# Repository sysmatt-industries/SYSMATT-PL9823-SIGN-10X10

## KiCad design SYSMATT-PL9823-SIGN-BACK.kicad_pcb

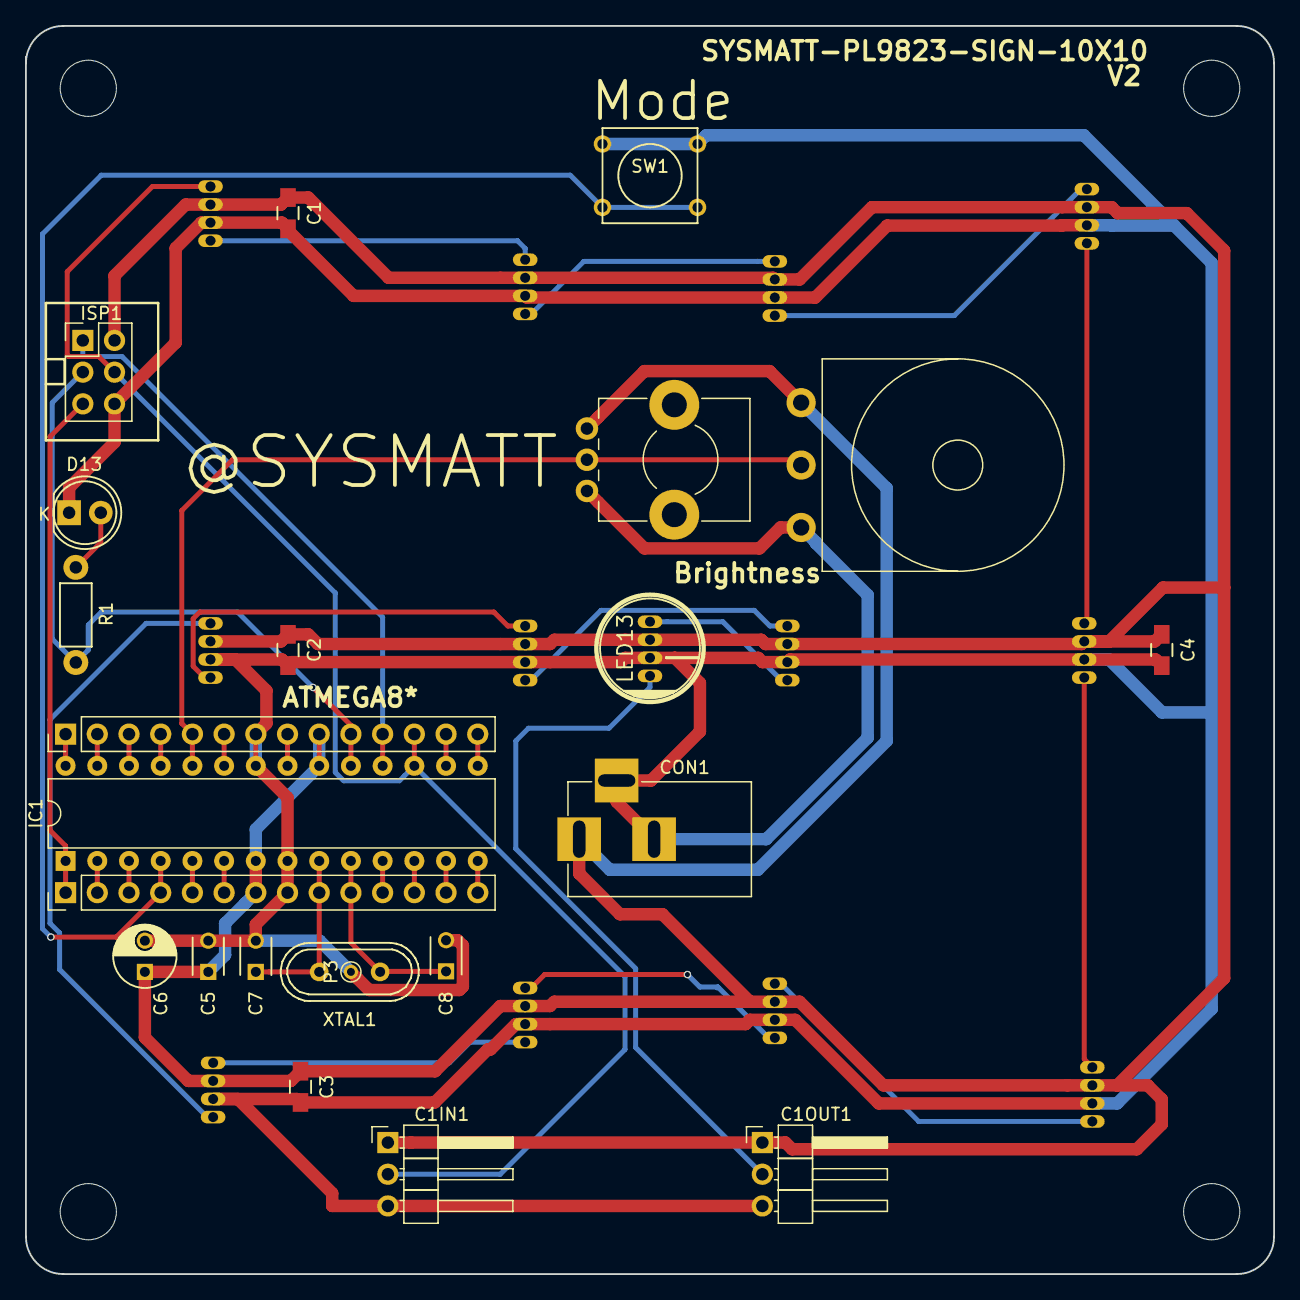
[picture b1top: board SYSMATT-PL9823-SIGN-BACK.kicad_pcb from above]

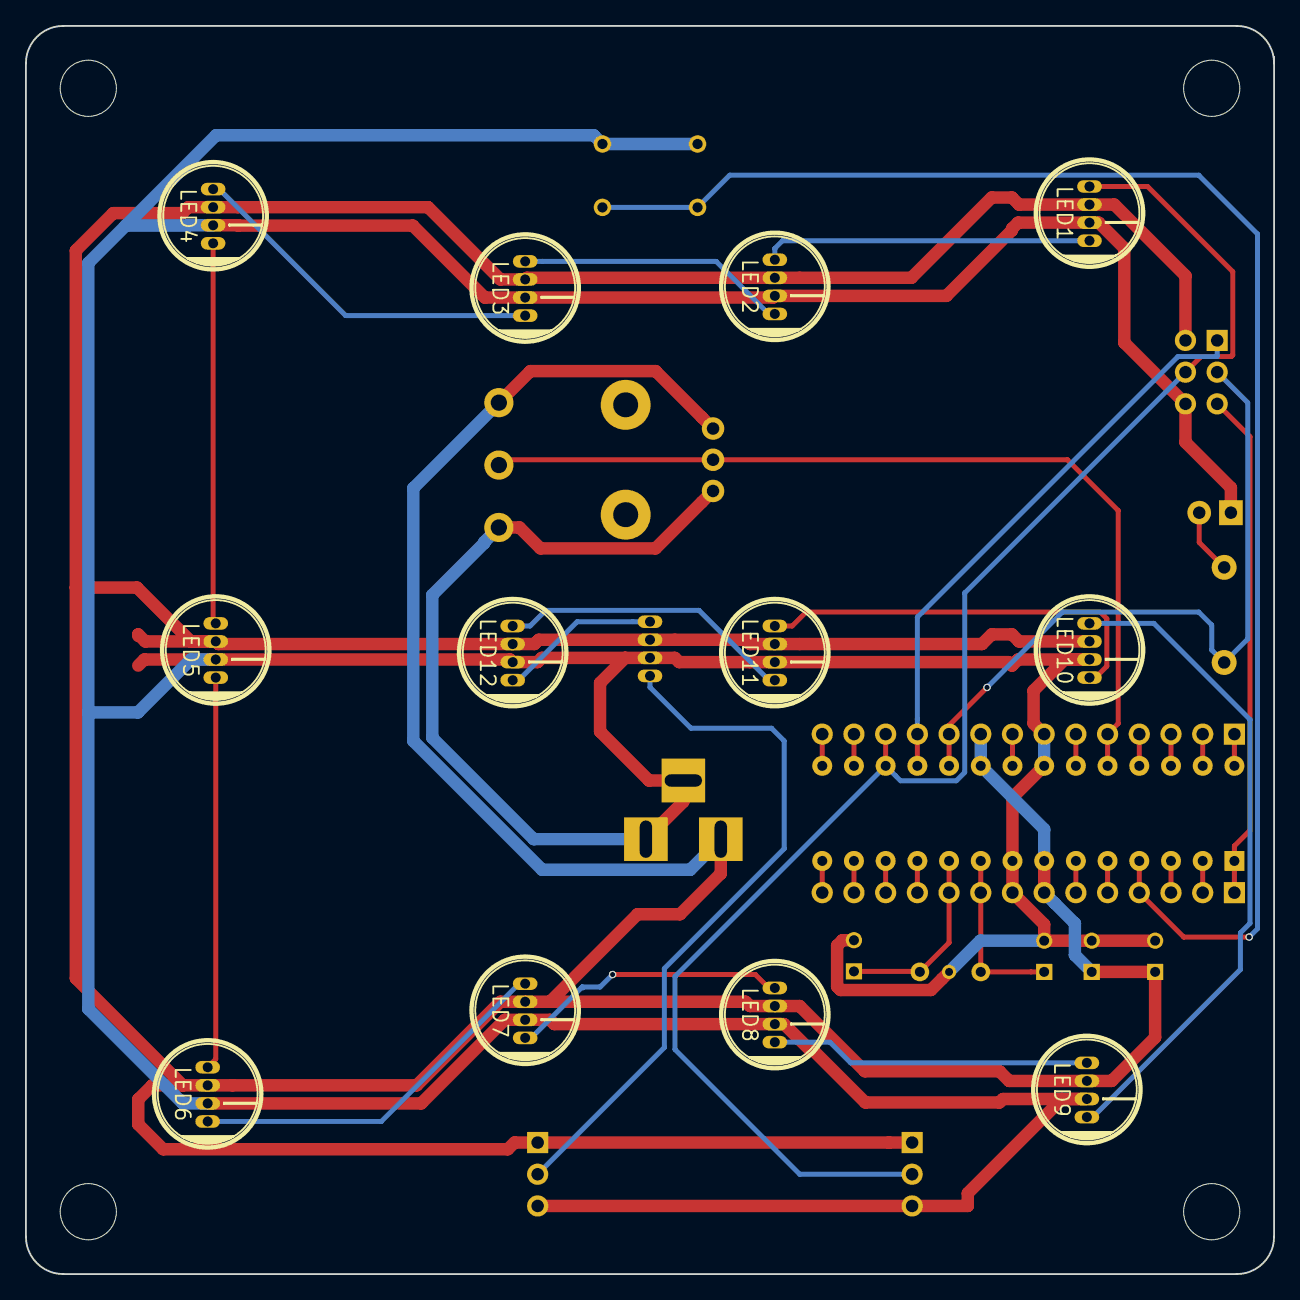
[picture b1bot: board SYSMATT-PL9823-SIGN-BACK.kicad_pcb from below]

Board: 2 copper layers, 100.0 x 100.0 mm, 35 parts (12 on the bottom side), 40 nets.

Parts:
C1, C2, C3, C4: CP1_Small; C_0805_HandSoldering
C1IN1, C1OUT1: CONN_01X03; Pin_Header_Angled_1x03_Pitch2.54mm
C5, C7, C8: C; C_Disc_D3_P2.5
C6: CP1; C_Radial_D5_L6_P2.5
CON1: BARREL_JACK
D13: LED; LED-5MM
IC1: ATMEGA8-P; DIP-28_W7.62mm
ISP1: CONN_02X03; Pin_Header_Straight_2x03_Pitch2.54mm
LED1, LED2, LED3, LED4, LED5, LED6, LED7, LED8, LED9, LED10, LED11, LED12, LED13: PL9823; PL9823-SYSMATT-V4
P1, P2: CONN_01X14; Pin_Header_Straight_1x14_Pitch2.54mm
P3: CONN_01X01; PINTST
R1: R; Resistor_Horizontal_RM7mm
RV1: POT; Potentiometer_Bourns_PTV09A-1_Horizontal
RV2: POT; Potentiometer_Omeg_PC16PU_Horizontal
SW1: SW_PUSH; SW_PUSH_SMALL
XTAL1: Crystal; Crystal_HC49-U_Vertical

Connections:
/DIN: C1IN1.2, IC1.17, ISP1.4, LED1.1, P2.12
/DOUT: C1OUT1.2, LED13.4
/SYSMATT-ATMEGA-ASP-BO/ATMEGA_ANALOG_POT: IC1.24, P2.5, RV1.2, RV2.2
/SYSMATT-ATMEGA-ASP-BO/ATMEGA_BUTTON_IN: IC1.4, P1.4, SW1.2
/SYSMATT-ATMEGA-ASP-BO/P1: IC1.1, ISP1.5, P1.1
/SYSMATT-ATMEGA-ASP-BO/P2: IC1.2, P1.2
/SYSMATT-ATMEGA-ASP-BO/P3: IC1.3, P1.3
/SYSMATT-ATMEGA-ASP-BO/P5: IC1.5, P1.5
/SYSMATT-ATMEGA-ASP-BO/P6: IC1.6, P1.6
/SYSMATT-ATMEGA-ASP-BO/P9: C7.1, IC1.9, P1.9, XTAL1.1
/SYSMATT-ATMEGA-ASP-BO/P10: C8.1, IC1.10, P1.10, XTAL1.2
/SYSMATT-ATMEGA-ASP-BO/P11: IC1.11, P1.11
/SYSMATT-ATMEGA-ASP-BO/P12: IC1.12, P1.12
/SYSMATT-ATMEGA-ASP-BO/P13: IC1.13, P1.13
/SYSMATT-ATMEGA-ASP-BO/P14: IC1.14, P1.14
/SYSMATT-ATMEGA-ASP-BO/P15: IC1.15, P2.14
/SYSMATT-ATMEGA-ASP-BO/P16: IC1.16, P2.13
/SYSMATT-ATMEGA-ASP-BO/P18: IC1.18, ISP1.1, P2.11
/SYSMATT-ATMEGA-ASP-BO/P19: IC1.19, ISP1.3, P2.10, R1.1
/SYSMATT-ATMEGA-ASP-BO/P21: IC1.21, P2.8
/SYSMATT-ATMEGA-ASP-BO/P23: IC1.23, P2.6
/SYSMATT-ATMEGA-ASP-BO/P25: IC1.25, P2.4
/SYSMATT-ATMEGA-ASP-BO/P26: IC1.26, P2.3
/SYSMATT-ATMEGA-ASP-BO/P27: IC1.27, P2.2
/SYSMATT-ATMEGA-ASP-BO/P28: IC1.28, P2.1
GND: C1.2, C1IN1.3, C1OUT1.3, C2.2, C3.2, C4.2, C5.2, C6.2, C7.2, C8.2, CON1.2, CON1.3, D13.1, IC1.8, IC1.22, ISP1.6, LED1.3, LED2.3, LED3.3, LED4.3, LED5.3, LED6.3, LED7.3, LED8.3, LED9.3, LED10.3, LED11.3, LED12.3, LED13.3, P1.8, P2.7, P3.1, RV1.1, RV2.1, SW1.1
unnamed: D13.2, R1.2
unnamed: LED1.4, LED2.1
unnamed: LED2.4, LED3.1
unnamed: LED3.4, LED4.1
unnamed: LED4.4, LED5.1
unnamed: LED5.4, LED6.1
unnamed: LED6.4, LED7.1
unnamed: LED7.4, LED8.1
unnamed: LED8.4, LED9.1
unnamed: LED9.4, LED10.1
unnamed: LED10.4, LED11.1
unnamed: LED11.4, LED12.1
unnamed: LED12.4, LED13.1
VCC: C1.1, C1IN1.1, C1OUT1.1, C2.1, C3.1, C4.1, C5.1, C6.1, CON1.1, IC1.7, IC1.20, ISP1.2, LED1.2, LED2.2, LED3.2, LED4.2, LED5.2, LED6.2, LED7.2, LED8.2, LED9.2, LED10.2, LED11.2, LED12.2, LED13.2, P1.7, P2.9, RV1.3, RV2.3

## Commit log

2017-04-14 Initial Upload of selected project files
2017-04-14 Arduino Code Upload
